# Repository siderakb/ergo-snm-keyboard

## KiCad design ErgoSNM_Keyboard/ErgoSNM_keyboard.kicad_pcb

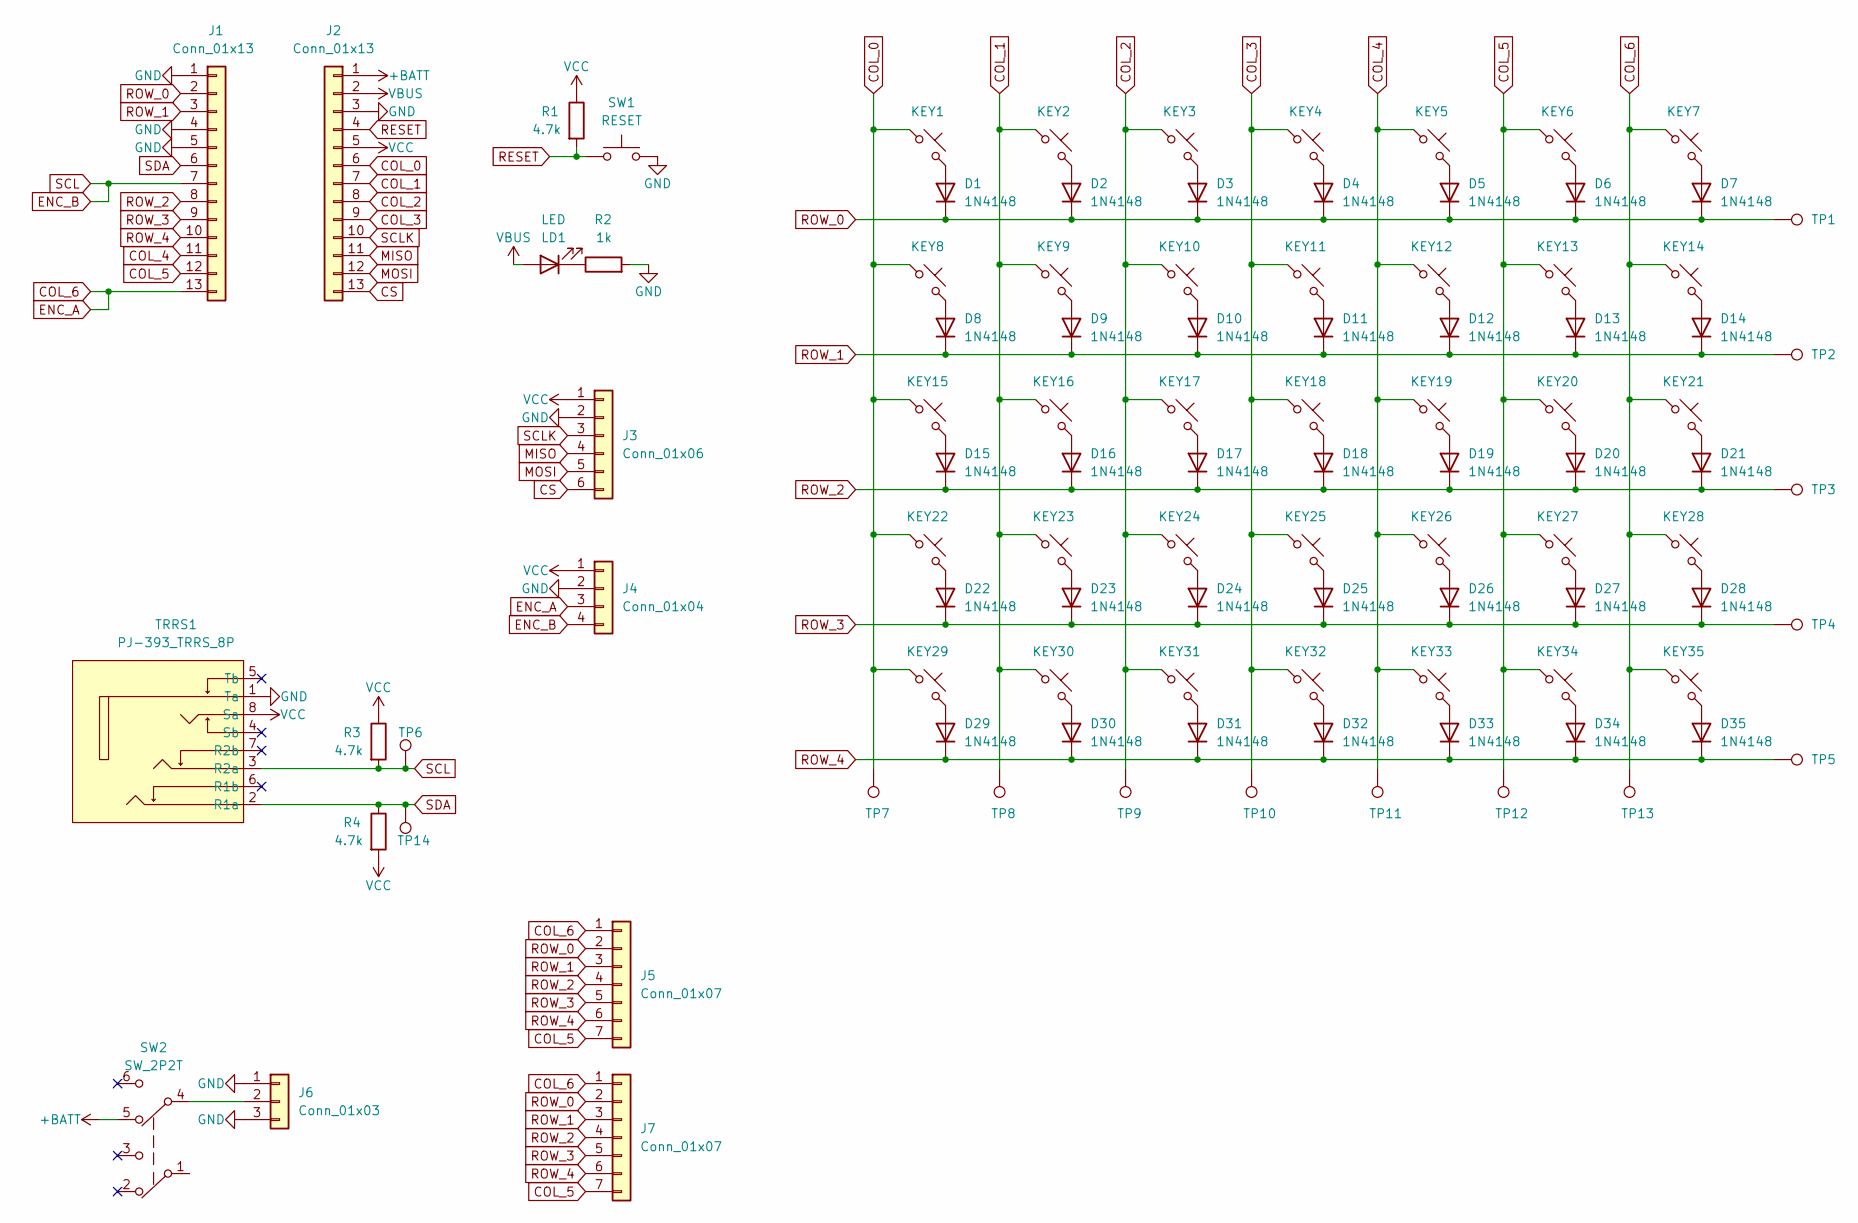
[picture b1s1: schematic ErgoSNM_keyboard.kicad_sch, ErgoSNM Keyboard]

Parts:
D1, D2, D3, D4, D5, D6, D7, D8, D9, D10, D11, D12, D13, D14, D15, D16, D17, D18, D19, D20, D21, D22, D23, D24, D25, D26, D27, D28, D29, D30, D31, D32, D33, D34, D35: 1N4148; D_0603_1608Metric
J1, J2: Conn_01x13; PinSocket_1x13_P2.54mm_Vertical
J3: Conn_01x06; PinHeader_1x06_P2.54mm_Vertical
J4: Conn_01x04; PinHeader_1x04_P2.54mm_Vertical
J5, J7: Conn_01x07; PinHeader_1x07_P2.54mm_Vertical
J6: Conn_01x03; JST_PH_B3B-PH-K_1x03_P2.00mm_Vertical
KEY1, KEY2, KEY3, KEY4, KEY5, KEY6, KEY7, KEY8, KEY9, KEY10, KEY11, KEY12, KEY13, KEY14, KEY15, KEY16, KEY17, KEY18, KEY19, KEY20, KEY21, KEY22, KEY23, KEY24, KEY25, KEY26, KEY27, KEY28, KEY29, KEY30, KEY31, KEY32, KEY33, KEY34, KEY35: SW_Push_45deg; MX_switch_THT_hotswap_double_sided_A
LD1: LED; LED_0603_1608Metric
R1, R3, R4: 4.7k; R_0603_1608Metric
R2: 1k; R_0603_1608Metric
SW1: RESET; SW_Push_1P1T_NO_6x6mm_H9.5mm
SW2: SW_2P2T; MSK-23D20-T
TP1, TP2, TP3, TP4, TP5, TP6, TP7, TP8, TP9, TP10, TP11, TP12, TP13, TP14: TestPoint; TestPoint_Pad_D2.5mm
TRRS1: PJ-393_TRRS_8P; PJ-393

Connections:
+BATT: J2.1, SW2.5
COL_0: J2.6, KEY1.1, KEY8.1, KEY15.1, KEY22.1, KEY29.1, TP7.1
COL_1: J2.7, KEY2.1, KEY9.1, KEY16.1, KEY23.1, KEY30.1, TP8.1
COL_2: J2.8, KEY3.1, KEY10.1, KEY17.1, KEY24.1, KEY31.1, TP9.1
COL_3: J2.9, KEY4.1, KEY11.1, KEY18.1, KEY25.1, KEY32.1, TP10.1
COL_4: J1.11, KEY5.1, KEY12.1, KEY19.1, KEY26.1, KEY33.1, TP11.1
COL_5: J1.12, J5.7, J7.7, KEY6.1, KEY13.1, KEY20.1, KEY27.1, KEY34.1, TP12.1
COL_6: J1.13, J4.3, J5.1, J7.1, KEY7.1, KEY14.1, KEY21.1, KEY28.1, KEY35.1, TP13.1
CS: J2.13, J3.6
ENC_B: J1.7, J4.4, R3.2, TP6.1, TRRS1.3 (R2a)
GND: J1.1, J1.4, J1.5, J2.3, J3.2, J4.2, J6.1, J6.3, R2.2, SW1.2, TRRS1.1 (Ta)
MISO: J2.11, J3.4
MOSI: J2.12, J3.5
unnamed: D1.2 (A), KEY1.2
unnamed: D2.2 (A), KEY2.2
unnamed: D3.2 (A), KEY3.2
unnamed: D4.2 (A), KEY4.2
unnamed: D5.2 (A), KEY5.2
unnamed: D6.2 (A), KEY6.2
unnamed: D7.2 (A), KEY7.2
unnamed: D8.2 (A), KEY8.2
unnamed: D9.2 (A), KEY9.2
unnamed: D10.2 (A), KEY10.2
unnamed: D11.2 (A), KEY11.2
unnamed: D12.2 (A), KEY12.2
unnamed: D13.2 (A), KEY13.2
unnamed: D14.2 (A), KEY14.2
unnamed: D15.2 (A), KEY15.2
unnamed: D16.2 (A), KEY16.2
unnamed: D17.2 (A), KEY17.2
unnamed: D18.2 (A), KEY18.2
unnamed: D19.2 (A), KEY19.2
unnamed: D20.2 (A), KEY20.2
unnamed: D21.2 (A), KEY21.2
unnamed: D22.2 (A), KEY22.2
unnamed: D23.2 (A), KEY23.2
unnamed: D24.2 (A), KEY24.2
unnamed: D25.2 (A), KEY25.2
unnamed: D26.2 (A), KEY26.2
unnamed: D27.2 (A), KEY27.2
unnamed: D28.2 (A), KEY28.2
unnamed: D29.2 (A), KEY29.2
unnamed: D30.2 (A), KEY30.2
unnamed: D31.2 (A), KEY31.2
unnamed: D32.2 (A), KEY32.2
unnamed: D33.2 (A), KEY33.2
unnamed: D34.2 (A), KEY34.2
unnamed: D35.2 (A), KEY35.2
unnamed: J6.2, SW2.4
unnamed: LD1.1 (K), R2.1
RESET: J2.4, R1.2, SW1.1
ROW_0: D1.1 (K), D2.1 (K), D3.1 (K), D4.1 (K), D5.1 (K), D6.1 (K), D7.1 (K), J1.2, J5.2, J7.2, TP1.1
ROW_1: D8.1 (K), D9.1 (K), D10.1 (K), D11.1 (K), D12.1 (K), D13.1 (K), D14.1 (K), J1.3, J5.3, J7.3, TP2.1
ROW_2: D15.1 (K), D16.1 (K), D17.1 (K), D18.1 (K), D19.1 (K), D20.1 (K), D21.1 (K), J1.8, J5.4, J7.4, TP3.1
ROW_3: D22.1 (K), D23.1 (K), D24.1 (K), D25.1 (K), D26.1 (K), D27.1 (K), D28.1 (K), J1.9, J5.5, J7.5, TP4.1
ROW_4: D29.1 (K), D30.1 (K), D31.1 (K), D32.1 (K), D33.1 (K), D34.1 (K), D35.1 (K), J1.10, J5.6, J7.6, TP5.1
SCLK: J2.10, J3.3
SDA: J1.6, R4.1, TP14.1, TRRS1.2 (R1a)
VBUS: J2.2, LD1.2 (A)
VCC: J2.5, J3.1, J4.1, R1.1, R3.1, R4.2, TRRS1.8 (Sa)

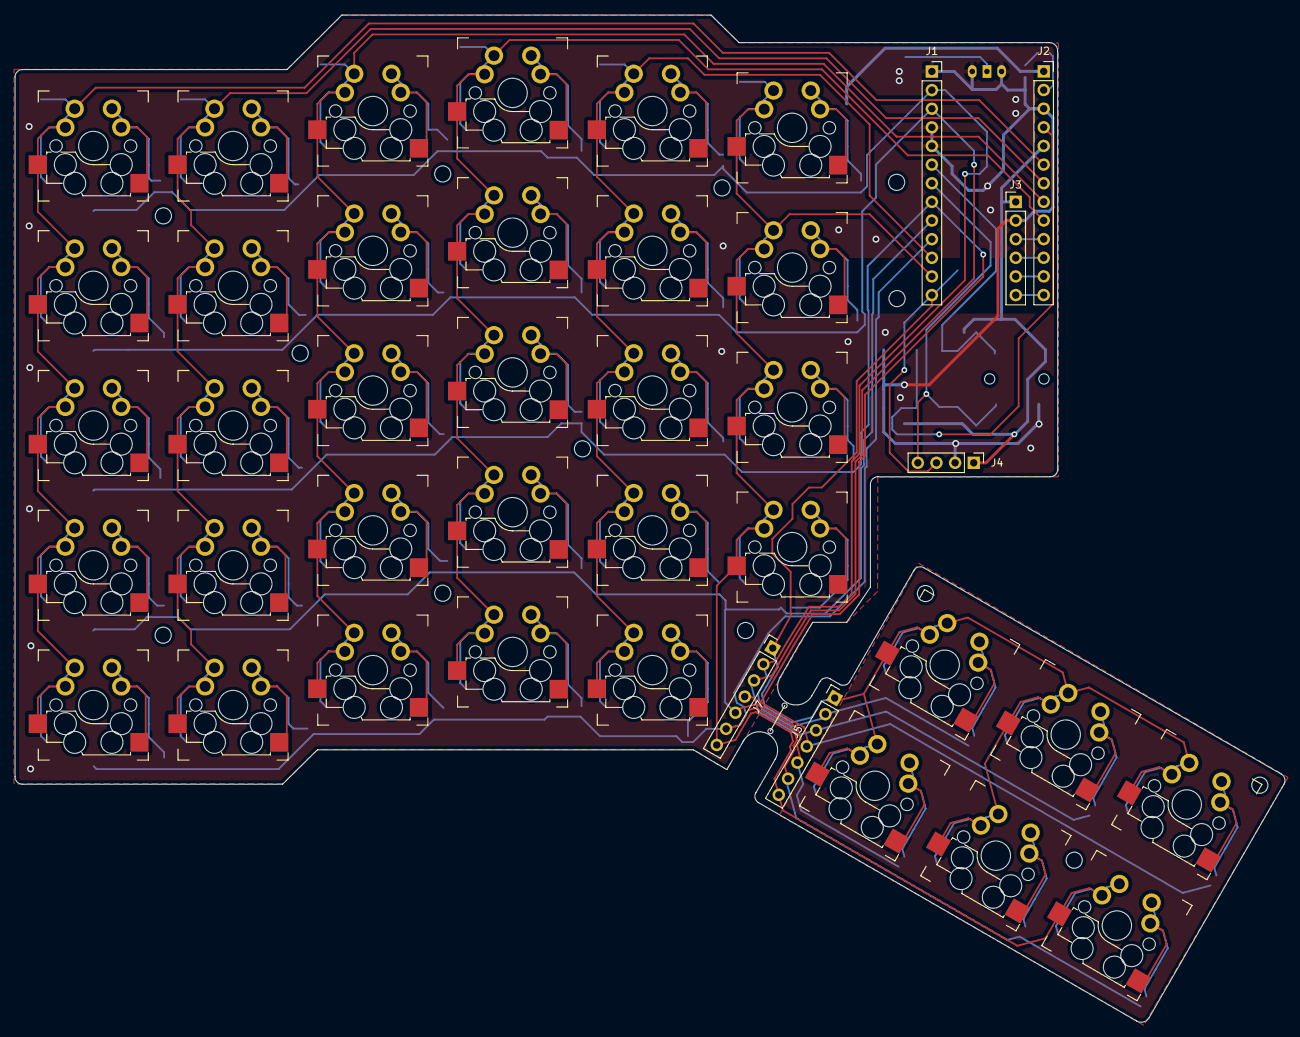
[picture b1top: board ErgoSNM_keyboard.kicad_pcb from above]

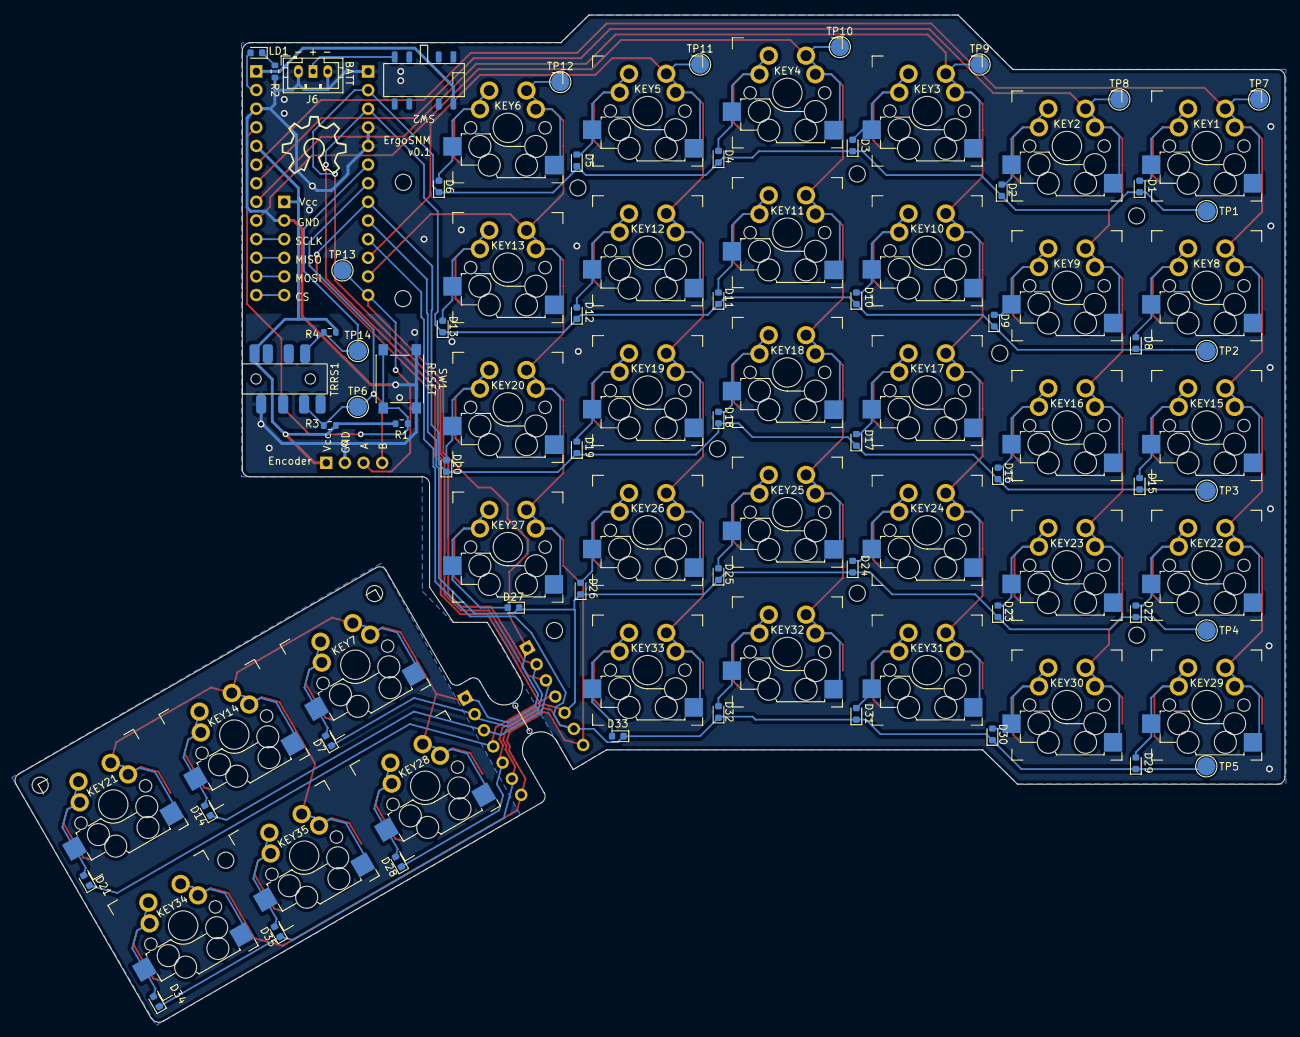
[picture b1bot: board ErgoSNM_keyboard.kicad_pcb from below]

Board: 2 copper layers, 173.1 x 137.3 mm, 99 parts (58 on the bottom side), 60 nets.

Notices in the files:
ErgoSNM_Keyboard/ErgoSNM_keyboard.kicad_pcb:
MIT License (Open source hardware)
